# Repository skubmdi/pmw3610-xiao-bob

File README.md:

# PMW3610-SUDU XIAO Breakoutboard
This product is a breakout board for the PMW3610-SUDU.
<br>It features a compact design that shares the same form factor as the Seeed Studio XIAO series.
<br>It operates exclusively at 3.3V and is designed to be used in conjunction with a XIAO module.

# Dimensional Drawing

- SMD components protrude 2 mm.<br>
- The lens protrudes 3 mm from the circuit board.<br>

# Pin Assign
## 2.54mm Pitch Pin Header

SDIO / SCLK / NCS / MOTION / 3V3 / GND

## 0.50mm Pitch FPC Connector

3V3 / MOTION / NCS / SCLK / SDIO / GND

# Kicad PCB Preview

# Mounted the SMD components and sensors

# With SeeedStudio XIAO (nRF52840-Plus)

# STL Sample
<i>under preparation</i>

# ZMK Sample
https://github.com/skubmdi/zmk-config-pmw3610-xiao

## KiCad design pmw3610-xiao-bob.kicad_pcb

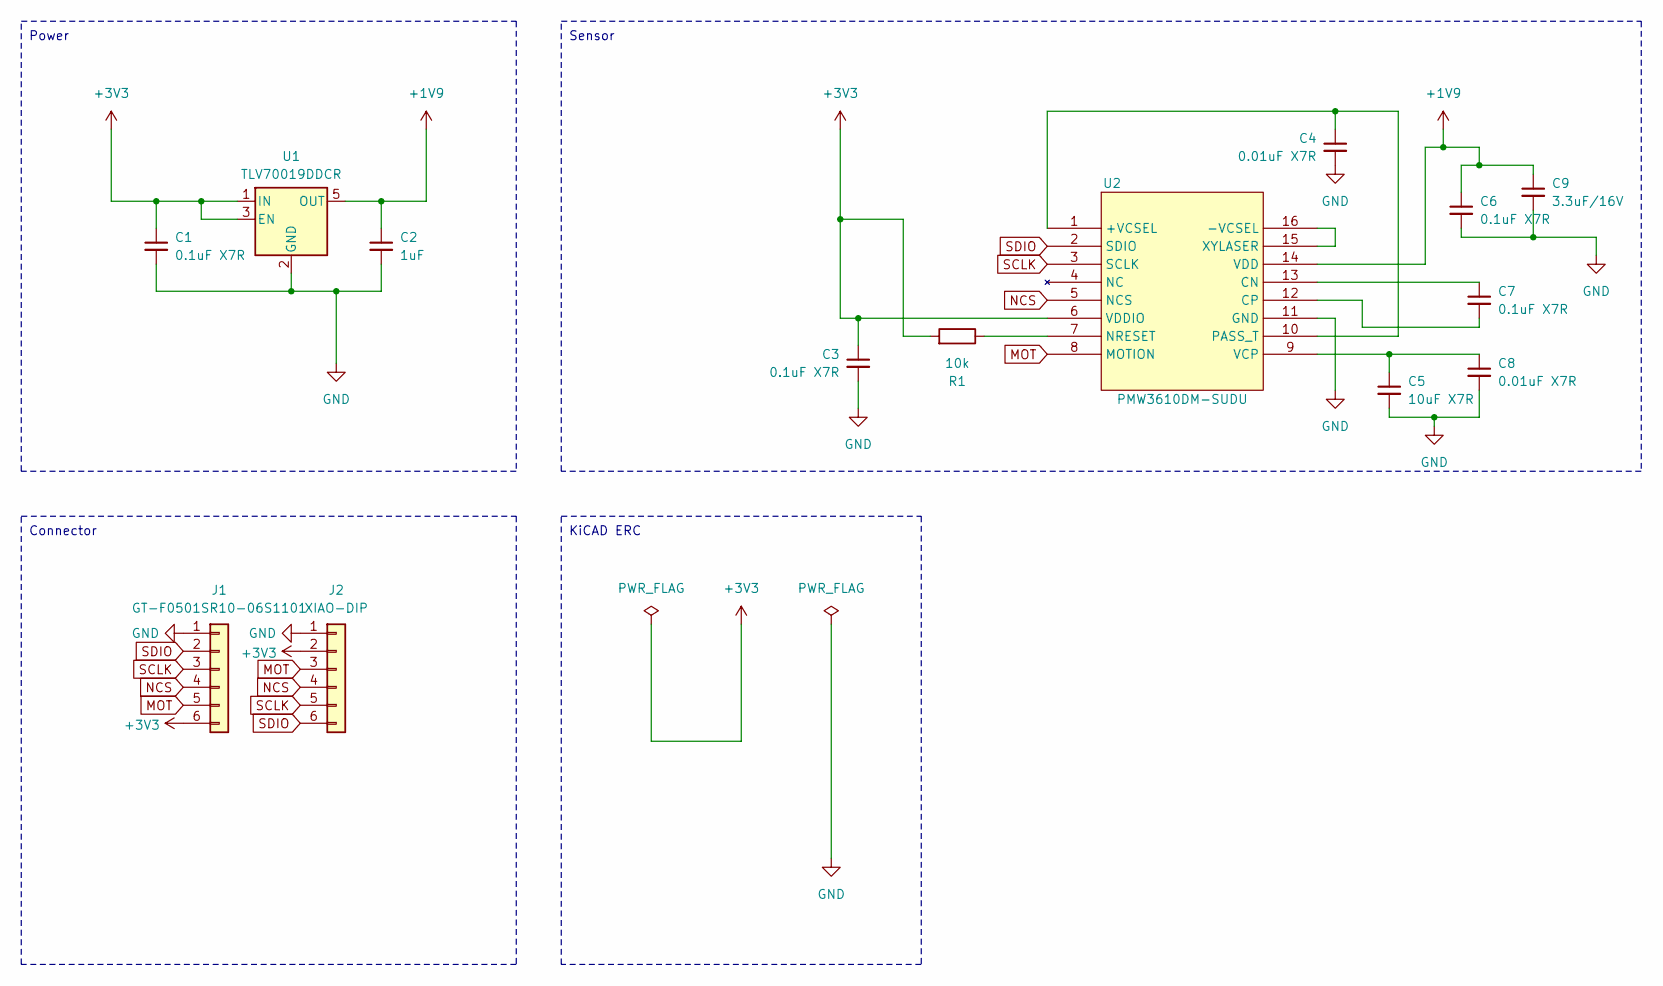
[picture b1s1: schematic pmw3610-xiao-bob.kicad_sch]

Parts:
C1, C3, C6, C7: 0.1uF X7R; C_0603_1608Metric
C2: 1uF; C_0603_1608Metric
C4, C8: 0.01uF X7R; C_0603_1608Metric
C5: 10uF X7R; C_0603_1608Metric
C9: 3.3uF/16V; C_0603_1608Metric
J1: GT-F0501SR10-06S1101
J2: XIAO-DIP
R1: 10k; R_0402_1005Metric
U1: TLV70019DDCR; SOT-23-5_HandSoldering
U2: PMW3610DM-SUDU

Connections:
+1V9: C2.1, C6.1, C9.1, U1.5 (OUT), U2.14 (VDD)
+3V3: C1.1, C3.1, J1.6, J2.2, R1.2, U1.1 (IN), U1.3 (EN), U2.6 (VDDIO)
GND: C1.2, C2.2, C3.2, C4.2, C5.2, C6.2, C8.2, C9.2, J1.1, J2.1, U1.2 (GND), U2.11 (GND)
MOT: J1.5, J2.3, U2.8 (MOTION)
NCS: J1.4, J2.4, U2.5 (NCS)
unnamed: C4.1, U2.1 (+VCSEL), U2.10 (PASS_T)
unnamed: U2.15 (XYLASER), U2.16 (-VCSEL)
unnamed: C7.1, U2.13 (CN)
unnamed: C7.2, U2.12 (CP)
unnamed: R1.1, U2.7 (NRESET)
unnamed: C5.1, C8.1, U2.9 (VCP)
SCLK: J1.3, J2.5, U2.3 (SCLK)
SDIO: J1.2, J2.6, U2.2 (SDIO)

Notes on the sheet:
Power
Sensor
Connector
KiCAD ERC

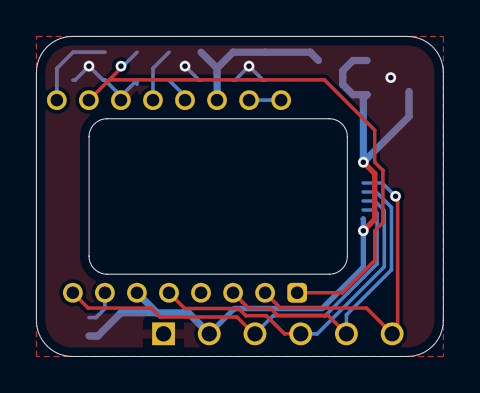
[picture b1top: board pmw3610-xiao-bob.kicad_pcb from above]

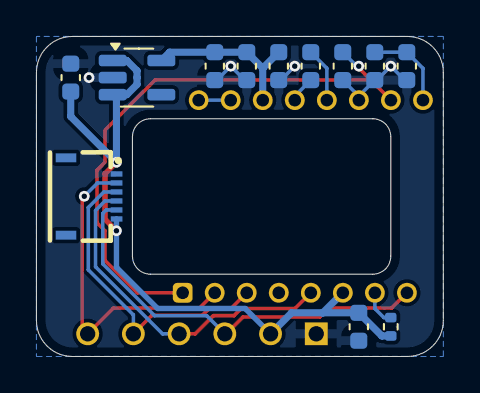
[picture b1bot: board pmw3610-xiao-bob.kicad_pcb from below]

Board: 2 copper layers, 22.6 x 17.8 mm, 14 parts (14 on the bottom side), 13 nets.

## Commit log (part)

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2026-06-30 init
2026-06-30 README
2026-06-30 LICENSE
